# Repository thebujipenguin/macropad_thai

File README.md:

# macropad_thai
Hackpad submission for Blueprint
the macropad it self is a 4x3 keypad with a knob and oled screen, i was inspired by adafruit industries rp2040 macropad.

# screenshots
Schematic

PCB

CAD

PCB and Schematic were done in KiCAD
3D model was done in fusion 360
i finally added the top case

# BOM
- 12x Cherry MX Switches
- 12x DSA Keycaps
- 12x 1N4148 DO-35 Diodes.
- 1x 0.91" 128x32 OLED Display
- 1x EC11 Rotary Encoder
- 1x XIAO RP2040
- 1x Case

# some other stuff
yo i had to finish this up in another country TT why'd you have to do this to me

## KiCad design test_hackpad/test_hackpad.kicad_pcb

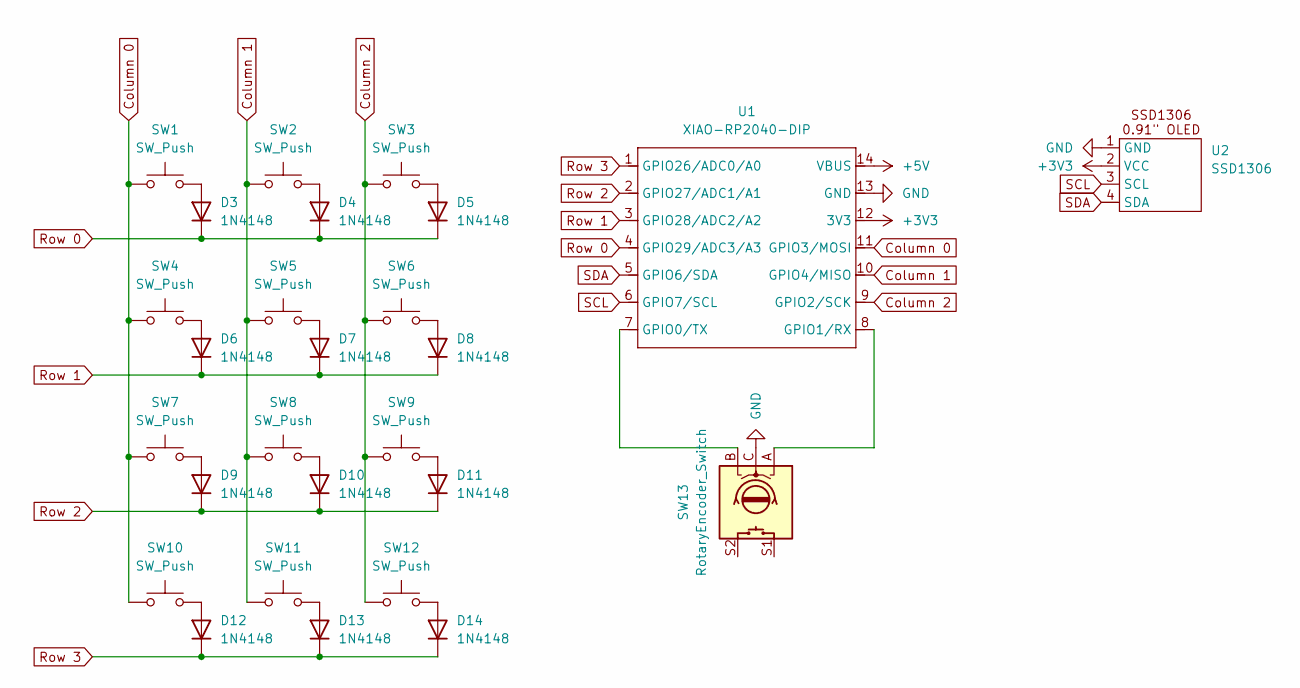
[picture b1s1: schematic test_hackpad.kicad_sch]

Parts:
D3, D4, D5, D6, D7, D8, D9, D10, D11, D12, D13, D14: 1N4148; D_DO-35_SOD27_P7.62mm_Horizontal
SW1, SW2, SW3, SW4, SW5, SW6, SW7, SW8, SW9, SW10, SW11, SW12: SW_Push; SW_Cherry_MX_1.00u_PCB
SW13: RotaryEncoder_Switch; RotaryEncoder_Alps_EC11E-Switch_Vertical_H20mm
U1: XIAO-RP2040-DIP
U2: SSD1306; SSD1306-0.91-OLED-4pin-128x32

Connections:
+3V3: U1.12 (3V3), U2.2 (VCC)
+5V: U1.14 (VBUS)
Column 0: SW1.1, SW4.1, SW7.1, SW10.1, U1.11 (GPIO3/MOSI)
Column 1: SW2.1, SW5.1, SW8.1, SW11.1, U1.10 (GPIO4/MISO)
Column 2: SW3.1, SW6.1, SW9.1, SW12.1, U1.9 (GPIO2/SCK)
GND: SW13.C, U1.13 (GND), U2.1 (GND)
unnamed: D3.2 (A), SW1.2
unnamed: D4.2 (A), SW2.2
unnamed: D5.2 (A), SW3.2
unnamed: D6.2 (A), SW4.2
unnamed: D7.2 (A), SW5.2
unnamed: D8.2 (A), SW6.2
unnamed: D9.2 (A), SW7.2
unnamed: D10.2 (A), SW8.2
unnamed: D11.2 (A), SW9.2
unnamed: D12.2 (A), SW10.2
unnamed: D13.2 (A), SW11.2
unnamed: D14.2 (A), SW12.2
unnamed: SW13.B, U1.7 (GPIO0/TX)
unnamed: SW13.A, U1.8 (GPIO1/RX)
Row 0: D3.1 (K), D4.1 (K), D5.1 (K), U1.4 (GPIO29/ADC3/A3)
Row 1: D6.1 (K), D7.1 (K), D8.1 (K), U1.3 (GPIO28/ADC2/A2)
Row 2: D9.1 (K), D10.1 (K), D11.1 (K), U1.2 (GPIO27/ADC1/A1)
Row 3: D12.1 (K), D13.1 (K), D14.1 (K), U1.1 (GPIO26/ADC0/A0)
SCL: U1.6 (GPIO7/SCL), U2.3 (SCL)
SDA: U1.5 (GPIO6/SDA), U2.4 (SDA)

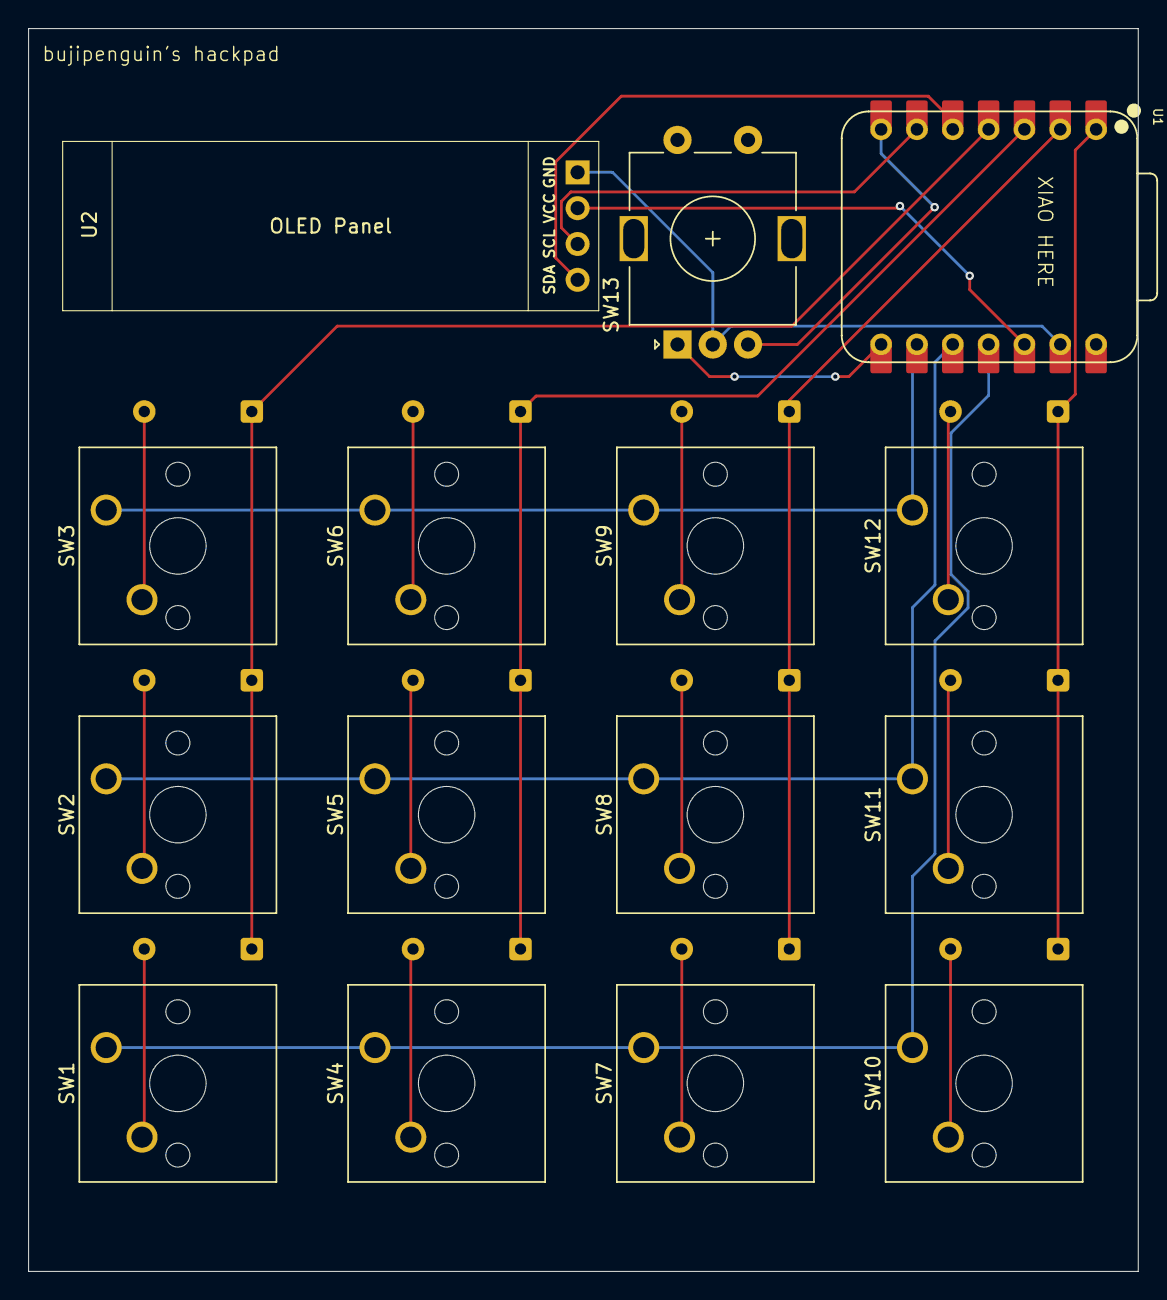
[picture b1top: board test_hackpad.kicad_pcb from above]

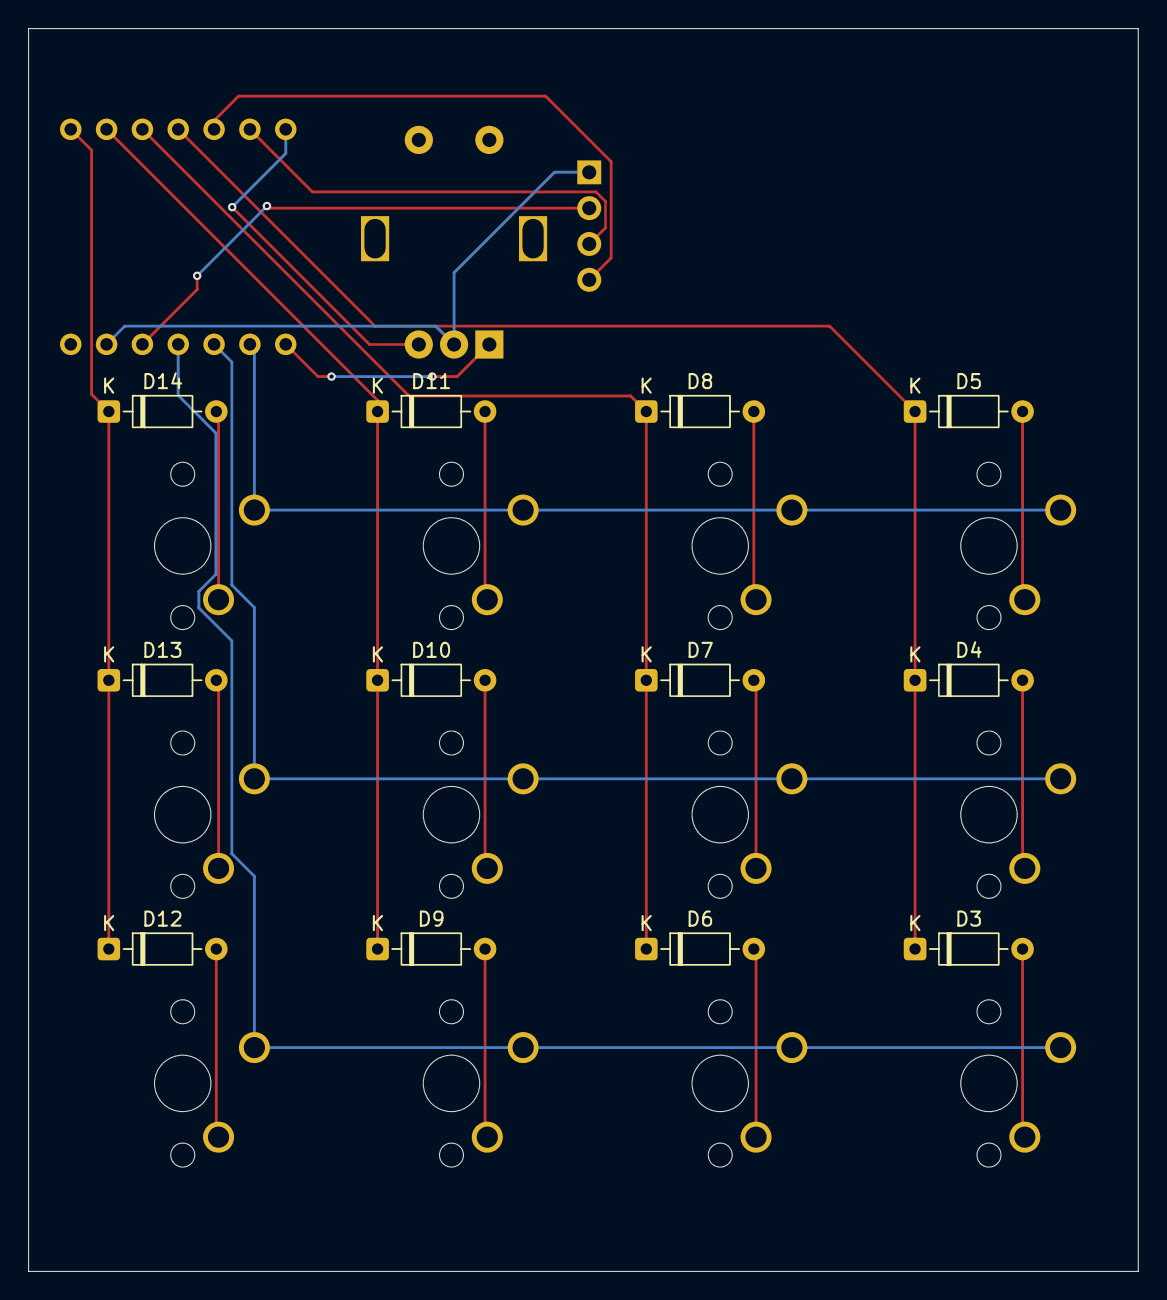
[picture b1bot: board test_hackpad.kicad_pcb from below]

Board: 2 copper layers, 78.7 x 88.1 mm, 27 parts (12 on the bottom side), 25 nets.

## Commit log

2025-12-22 Add README
2025-12-22 Added photos
2025-12-29 added top part of the case you meanies
